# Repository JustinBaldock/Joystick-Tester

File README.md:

# Remake-Tank-Mouse
Attempt to make a Joystick tester.

A small PCB with LEDs and a button battery. LEDs light up when joystick direction / buttons are pressed.

References;

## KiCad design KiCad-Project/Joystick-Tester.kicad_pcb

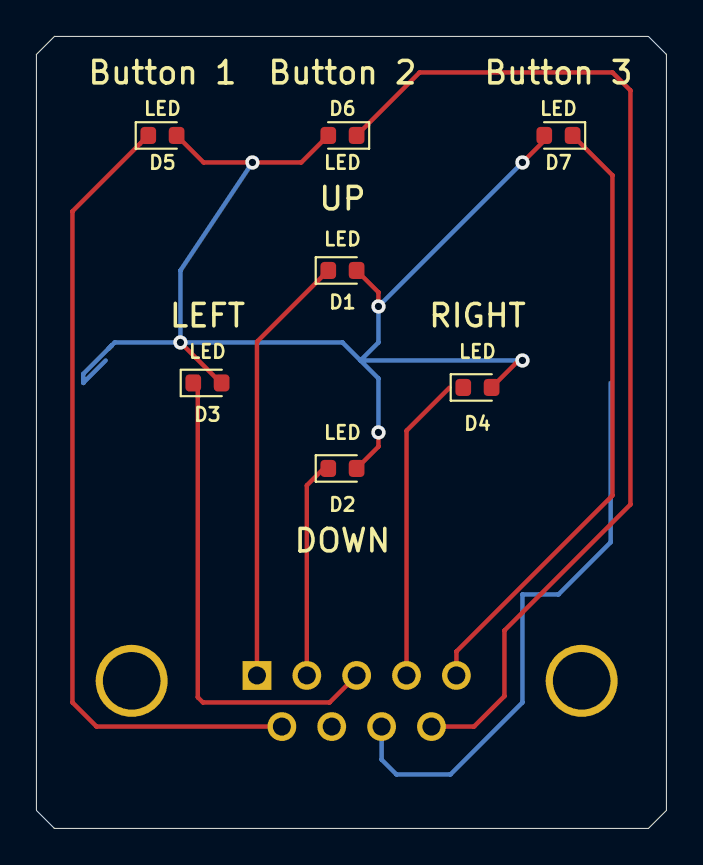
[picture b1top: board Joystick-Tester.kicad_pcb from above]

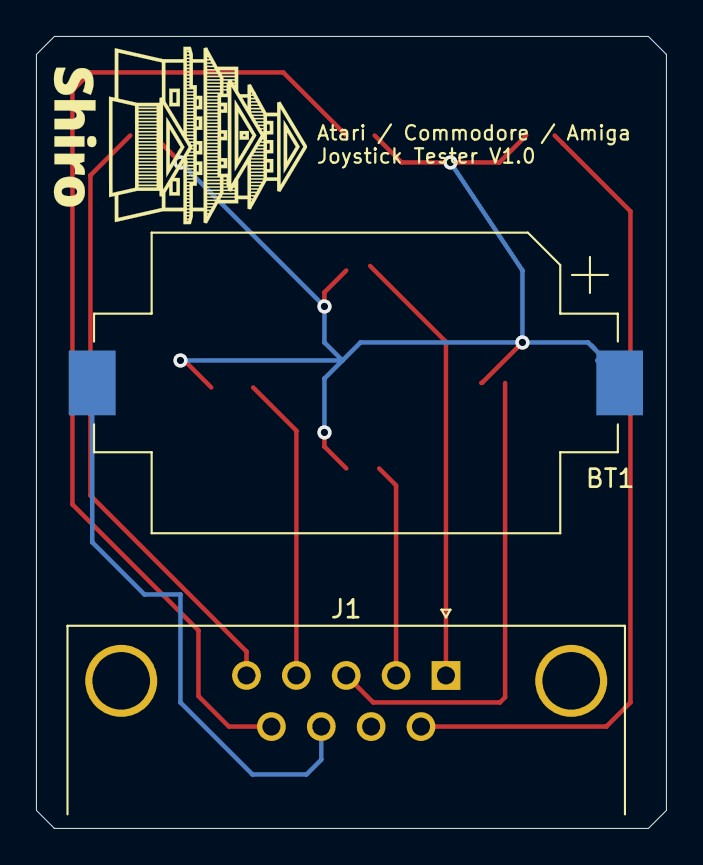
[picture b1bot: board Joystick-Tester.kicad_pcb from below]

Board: 2 copper layers, 35.0 x 44.0 mm, 9 parts (2 on the bottom side), 9 nets.

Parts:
BT1: Battery CR2032; BatteryHolder_Keystone_1060_1x2032
D1, D2, D3, D4, D5, D6, D7: LED; LED_0603_1608Metric
J1: DB9_Female; DSUB-9_Female_Horizontal_P2.77x2.84mm_EdgePinOffset4.94mm_H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

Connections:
Button1: D5.1, J1.6
Button2: D6.1, J1.9
Button3: D7.1, J1.5
Down: D2.1, J1.2
GND: BT1.2, J1.8
Left: D3.1, J1.3
Right: D4.1, J1.4
Up: D1.1, J1.1
VCC+3v: BT1.1, D1.2, D2.2, D3.2, D4.2, D5.2, D6.2, D7.2

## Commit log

2019-12-05 Initial build
2019-12-05 Adding my company logo and silk screen info to PCB
